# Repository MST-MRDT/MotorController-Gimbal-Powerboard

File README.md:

# MotorController-Gimbal-Powerboard

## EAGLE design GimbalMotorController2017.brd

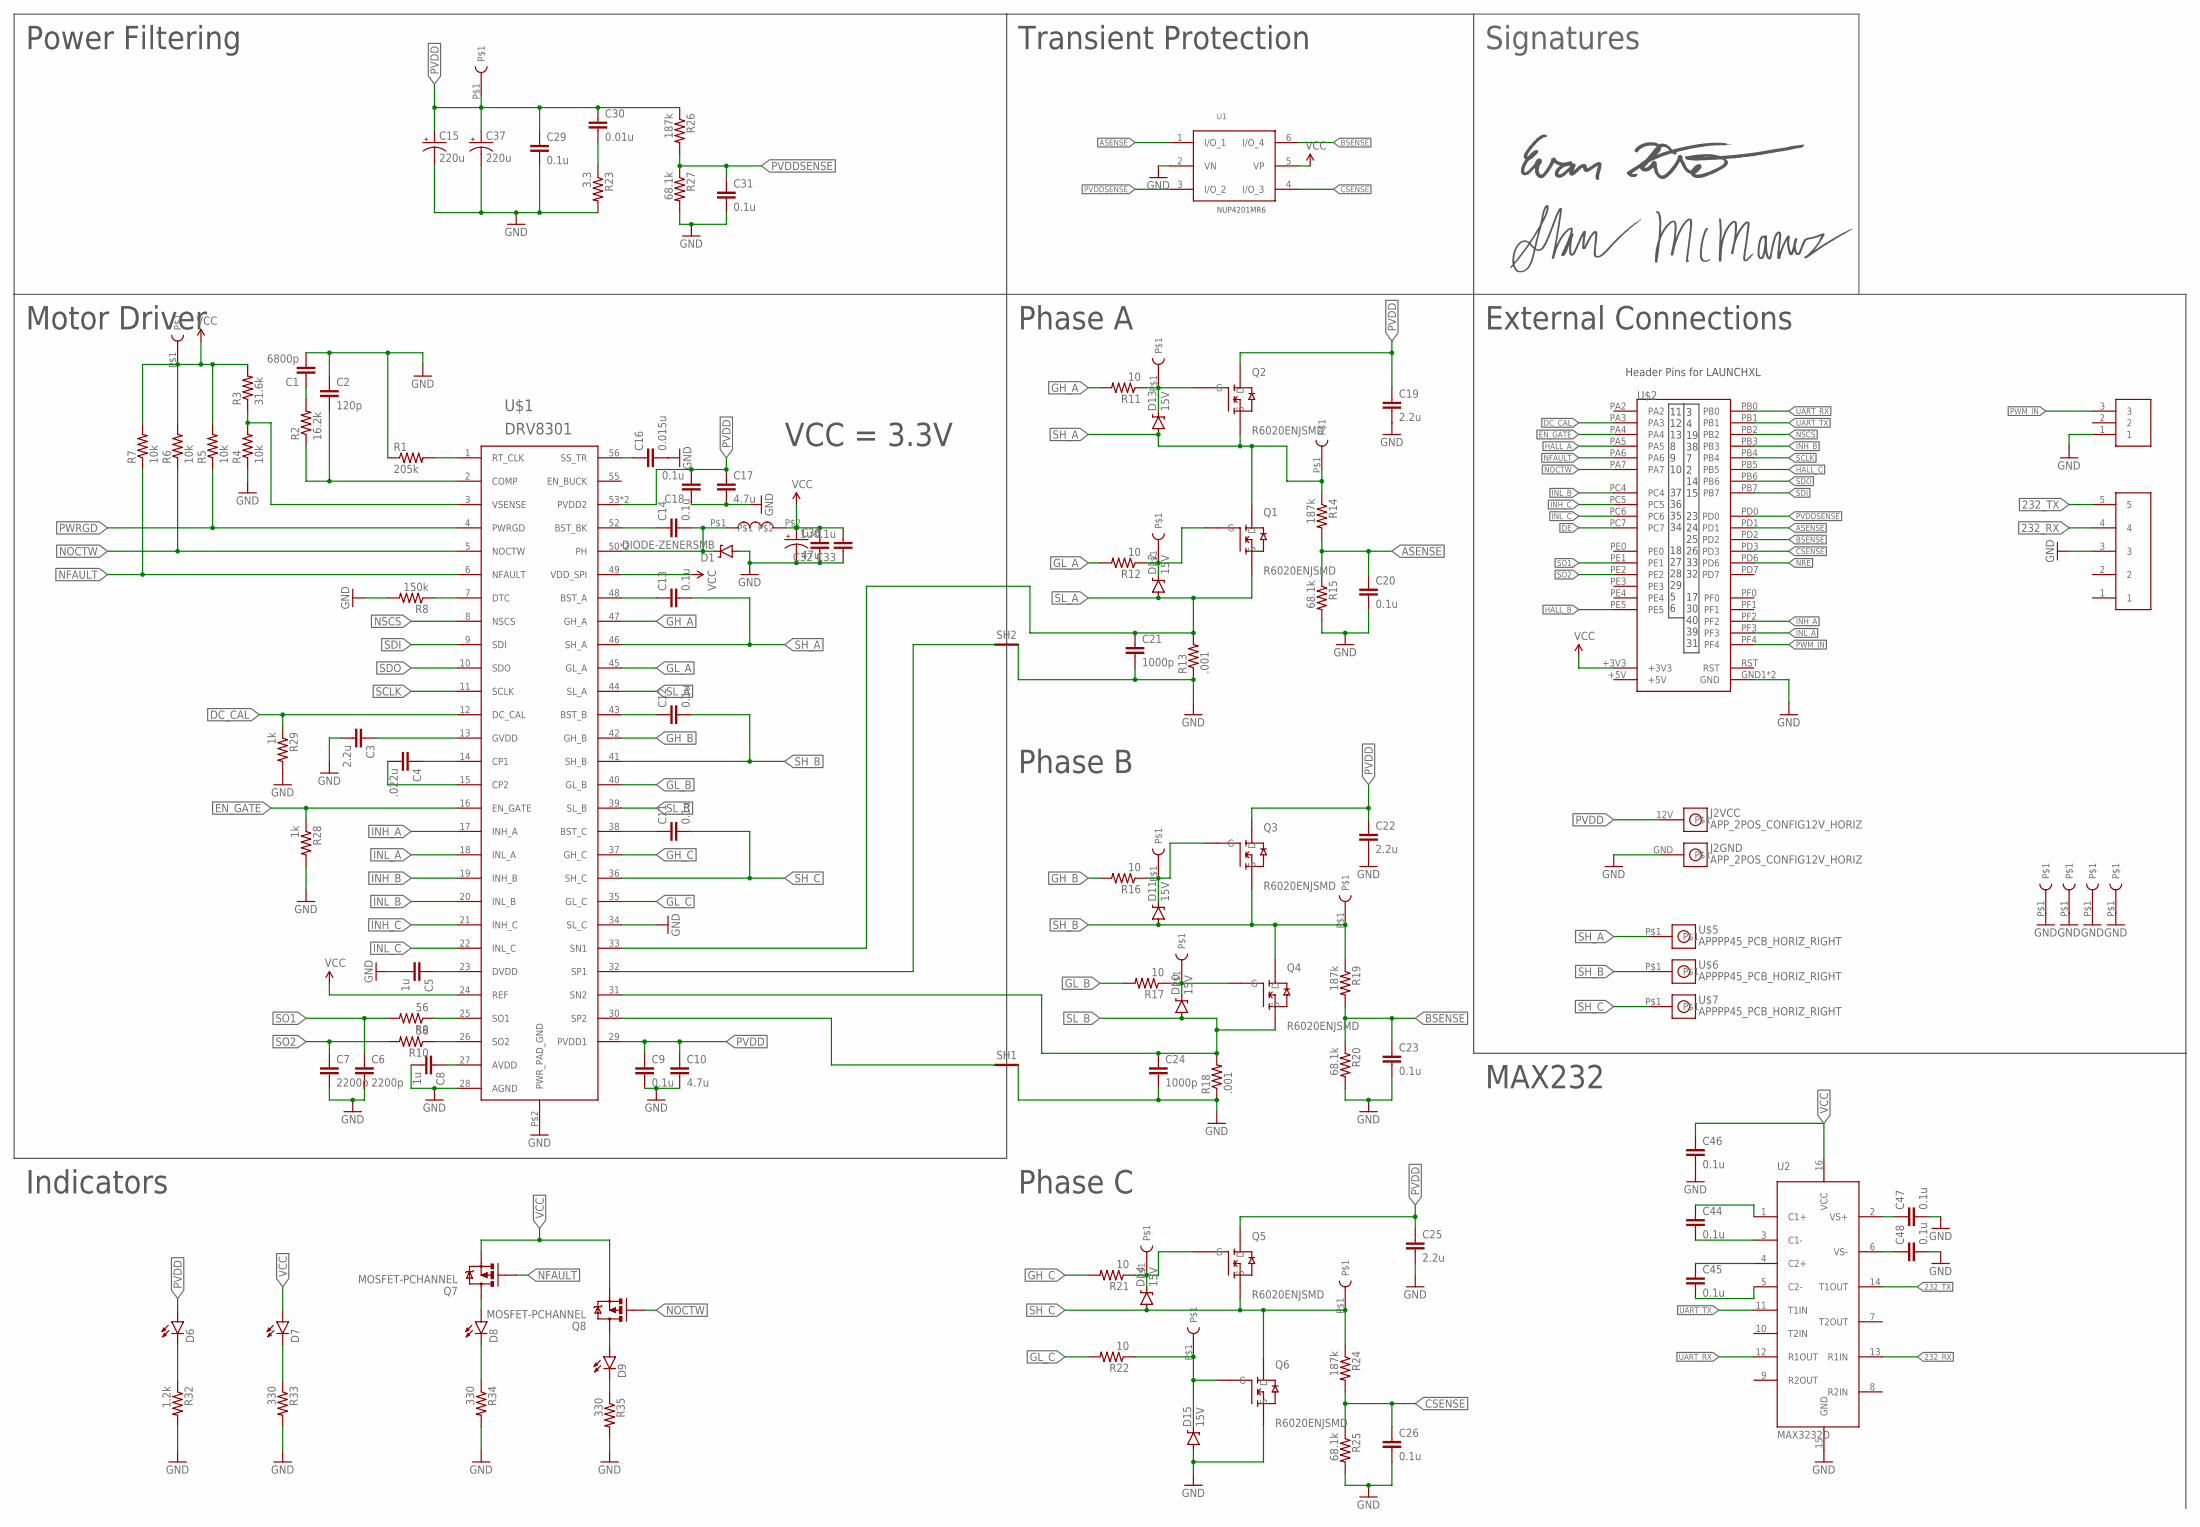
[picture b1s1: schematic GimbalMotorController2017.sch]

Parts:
C1: 6800p; 0805
C2: 120p; 0805
C3, C19, C22, C25: 2.2u; 1206
C4: .022u; 0805
C5, C8, C32: 1u; 0805
C6, C7: 2200p; 0805
C9, C11, C12, C13, C14, C18, C20, C23, C26, C29, C31, C33, C44, C45, C46, C47, C48: 0.1u; 0805
C10, C17: 4.7u; 1206
C15, C37: 220u; CPOL-RADIAL-1000UF-25V
C16: 0.015u; 0805
C21, C24: 1000p; 0805
C30: 0.01u; 0805
C36: 47u; CPOL-RADIAL-100UF-25V
D1: DIODE-ZENERSMB; SMB-DIODE
D6, D7, D8, D9: LED1206; LED-1206
D10, D11, D12, D13, D14, D15: 15V; SOD-323
J1: SL03THROUGH_HOLE; MOLEX_SL_03_TH
J2: APP_2POS_CONFIG12V_HORIZ; APP45_12V_HORIZ_CONFIG
Q1, Q2, Q3, Q4, Q5, Q6: R6020ENJSMD; D2PACK
Q7, Q8: MOSFET-PCHANNEL; SOT23-3
R1: 205k; 0805
R2: 16.2k; 0805
R3: 31.6k; 0805
R4, R5, R6, R7: 10k; 0805
R8: 150k; 0805
R9, R10: 56; 0805
R11, R12, R16, R17, R21, R22: 10; 0805
R13, R18: .001; 1206
R14, R19, R24, R26: 187k; 0805
R15, R20, R25, R27: 68.1k; 0805
R23: 3.3; 0805
R28, R29: 1k; 0805
R32: 1.2k; 0805
R33, R34, R35: 330; 0805
SH1, SH2: SHORT-HT5; SHORT_TOP-50
U1: NUP4201MR6; TSOP-6
U2: MAX3232D; SOIC16
U$1: DRV8301; TFSOP-56
U$2: TIVA-C
U$3, U$10, U$12, U$15, U$16, U$17, U$18, U$19, U$20, U$24, U$25, U$26, U$27, U$28, U$29: TEST_POINT_0.1INDIAM
U$4: 5PIN
U$5, U$6, U$7: APPPP45_PCB_HORIZ_RIGHT; APP45_PCB_HORIZ_RIGHT
U$8: SHAUN_MCMANUS_SIGNATURE
U$11: EVAN_HITE_SIGNATURE
U$14: 33u; INDUCTOR_DR74

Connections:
232_RX: U2.13 (R1IN), U$4.4
232_TX: U2.14 (T1OUT), U$4.5
+5V: U$2.+5V
ASENSE: C20.1, R14.2, R15.1, U1.1 (I/O_1), U$2.PD1
BSENSE: C23.1, R19.2, R20.1, U1.6 (I/O_4), U$2.PD2
CSENSE: C26.1, R24.2, R25.1, U1.4 (I/O_3), U$2.PD3
DC_CAL: R29.1, U$1.12 (DC_CAL), U$2.PA3
DE: U$2.PC7
EN_GATE: R28.1, U$1.16 (EN_GATE), U$2.PA4
GH_A: R11.2, U$1.47 (GH_A)
GH_B: R16.2, U$1.42 (GH_B)
GH_C: R21.2, U$1.37 (GH_C)
GL_A: R12.2, U$1.45 (GL_A)
GL_B: R17.2, U$1.40 (GL_B)
GL_C: R22.2, U$1.35 (GL_C)
GND: C1.2, C2.1, C3.2, C5.2, C6.2, C7.2, C8.2, C9.2, C10.2, C15.2 (-), C16.2, C17.2, C18.1, C19.2, C20.2, C21.2, C22.2, C23.2, C24.2, C25.2, C26.2, C29.2, C31.2, C32.1, C33.1, C36.2 (-), C37.2 (-), C46.2, C47.2, C48.2, D1.A, D15.A, J1.1, J2.GND, Q6.2 (S), R1.1, R4.1, R8.2, R13.1, R15.2, R18.1, R20.2, R23.2, R25.2, R27.2, R28.2, R29.2, R32.2, R33.2, R34.2, R35.2, SH1.2, SH2.2, U1.2 (VN), U2.15 (GND), U$1.28 (AGND), U$1.34 (SL_C), U$1.P$2 (PWR_PAD_GND), U$2.GND1 (GND), U$2.GND2 (GND), U$4.3, U$26.P$1, U$27.P$1, U$28.P$1, U$29.P$1
HALL_A: U$2.PA5
HALL_B: U$2.PE5
HALL_C: U$2.PB5
INH_A: U$1.17 (INH_A), U$2.PF2
INH_B: U$1.19 (INH_B), U$2.PB3
INH_C: U$1.21 (INH_C), U$2.PC5
INL_A: U$1.18 (INL_A), U$2.PF3
INL_B: U$1.20 (INL_B), U$2.PC4
INL_C: U$1.22 (INL_C), U$2.PC6
unnamed: C2.2, R2.1, U$1.2 (COMP)
unnamed: C1.1, R2.2
unnamed: R3.1, R4.2, U$1.3 (VSENSE)
unnamed: R1.2, U$1.1 (RT_CLK)
unnamed: R8.1, U$1.7 (DTC)
unnamed: C4.1, U$1.14 (CP1)
unnamed: C4.2, U$1.15 (CP2)
unnamed: C3.1, U$1.13 (GVDD)
unnamed: C5.1, U$1.23 (DVDD)
unnamed: R9.1, U$1.25 (SO1)
unnamed: R10.1, U$1.26 (SO2)
unnamed: C8.1, U$1.27 (AVDD)
unnamed: D13.C, Q2.1 (G), R11.1, U$12.P$1
unnamed: D11.C, Q3.1 (G), R16.1, U$16.P$1
unnamed: D10.C, Q4.1 (G), R17.1, U$17.P$1
unnamed: D12.C, Q1.1 (G), R12.1, U$15.P$1
unnamed: D14.C, Q5.1 (G), R21.1, U$18.P$1
unnamed: D15.C, Q6.1 (G), R22.1, U$19.P$1
unnamed: C11.1, U$1.38 (BST_C)
unnamed: C30.2, R23.1
unnamed: D6.C, R32.1
unnamed: D7.C, R33.1
unnamed: C12.1, U$1.43 (BST_B)
unnamed: D8.C, R34.1
unnamed: D9.C, R35.1
unnamed: D9.A, Q8.3 (D)
unnamed: C13.1, U$1.48 (BST_A)
unnamed: C14.1, U$1.52 (BST_BK)
unnamed: C14.2, D1.C, U$1.50 (PH), U$1.51 (PH), U$14.P$1
unnamed: D8.A, Q7.3 (D)
unnamed: C16.1, U$1.56 (SS_TR)
unnamed: C44.1, U2.1 (C1+)
unnamed: C44.2, U2.3 (C1-)
unnamed: C45.1, U2.4 (C2+)
unnamed: C45.2, U2.5 (C2-)
unnamed: C48.1, U2.6 (VS-)
unnamed: C47.1, U2.2 (VS+)
NFAULT: Q7.1 (G), R7.1, U$1.6 (NFAULT), U$2.PA6
NOCTW: Q8.1 (G), R6.1, U$1.5 (NOCTW), U$2.PA7
NRE: U$2.PD6
NSCS: U$1.8 (NSCS), U$2.PB2
PVDD: C9.1, C10.1, C15.1 (+), C17.1, C18.2, C19.1, C22.1, C25.1, C29.1, C30.1, C37.1 (+), D6.A, J2.12V, Q2.TAB (D), Q3.TAB (D), Q5.TAB (D), R26.1, U$1.29 (PVDD1), U$1.53 (PVDD2), U$1.54 (PVDD2), U$3.P$1
PVDDSENSE: C31.1, R26.2, R27.1, U1.3 (I/O_2), U$2.PD0
PWM_IN: J1.3, U$2.PF4
PWRGD: R5.1, U$1.4 (PWRGD)
RST: U$2.RST
SCLK: U$1.11 (SCLK), U$2.PB4
SDI: U$1.9 (SDI), U$2.PB7
SDO: U$1.10 (SDO), U$2.PB6
SH_A: C13.2, D13.A, Q1.TAB (D), Q2.2 (S), R14.1, U$1.46 (SH_A), U$5.P$1, U$25.P$1
SH_B: C12.2, D11.A, Q3.2 (S), Q4.TAB (D), R19.1, U$1.41 (SH_B), U$6.P$1, U$24.P$1
SH_C: C11.2, D14.A, Q5.2 (S), Q6.TAB (D), R24.1, U$1.36 (SH_C), U$7.P$1, U$20.P$1
SL_A: C21.1, D12.A, Q1.2 (S), R13.2, U$1.33 (SN1), U$1.44 (SL_A)
SL_B: C24.1, D10.A, Q4.2 (S), R18.2, U$1.31 (SN2), U$1.39 (SL_B)
SO1: C6.1, R9.2, U$2.PE1
SO2: C7.1, R10.2, U$2.PE2
SP1: SH2.1, U$1.32 (SP1)
SP2: SH1.1, U$1.30 (SP2)
UART_RX: U2.12 (R1OUT), U$2.PB0
UART_TX: U2.11 (T1IN), U$2.PB1
VCC: C32.2, C33.2, C36.1 (+), C46.1, D7.A, Q7.2 (S), Q8.2 (S), R3.2, R5.2, R6.2, R7.2, U1.5 (VP), U2.16 (VCC), U$1.24 (REF), U$1.49 (VDD_SPI), U$2.+3V3, U$10.P$1, U$14.P$2

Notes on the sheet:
11 12 13 8 9 10 37 36 35 34 18 27 28 29 5 6
3 4 19 38 7 2 14 15 23 24 25 26 33 32 17 30 40 39 31
Header Pins for LAUNCHXL
Power Filtering
Motor Driver
Transient Protection
Phase A
Phase B
Phase C
External Connections
Indicators
VCC = 3.3V
MAX232
Signatures

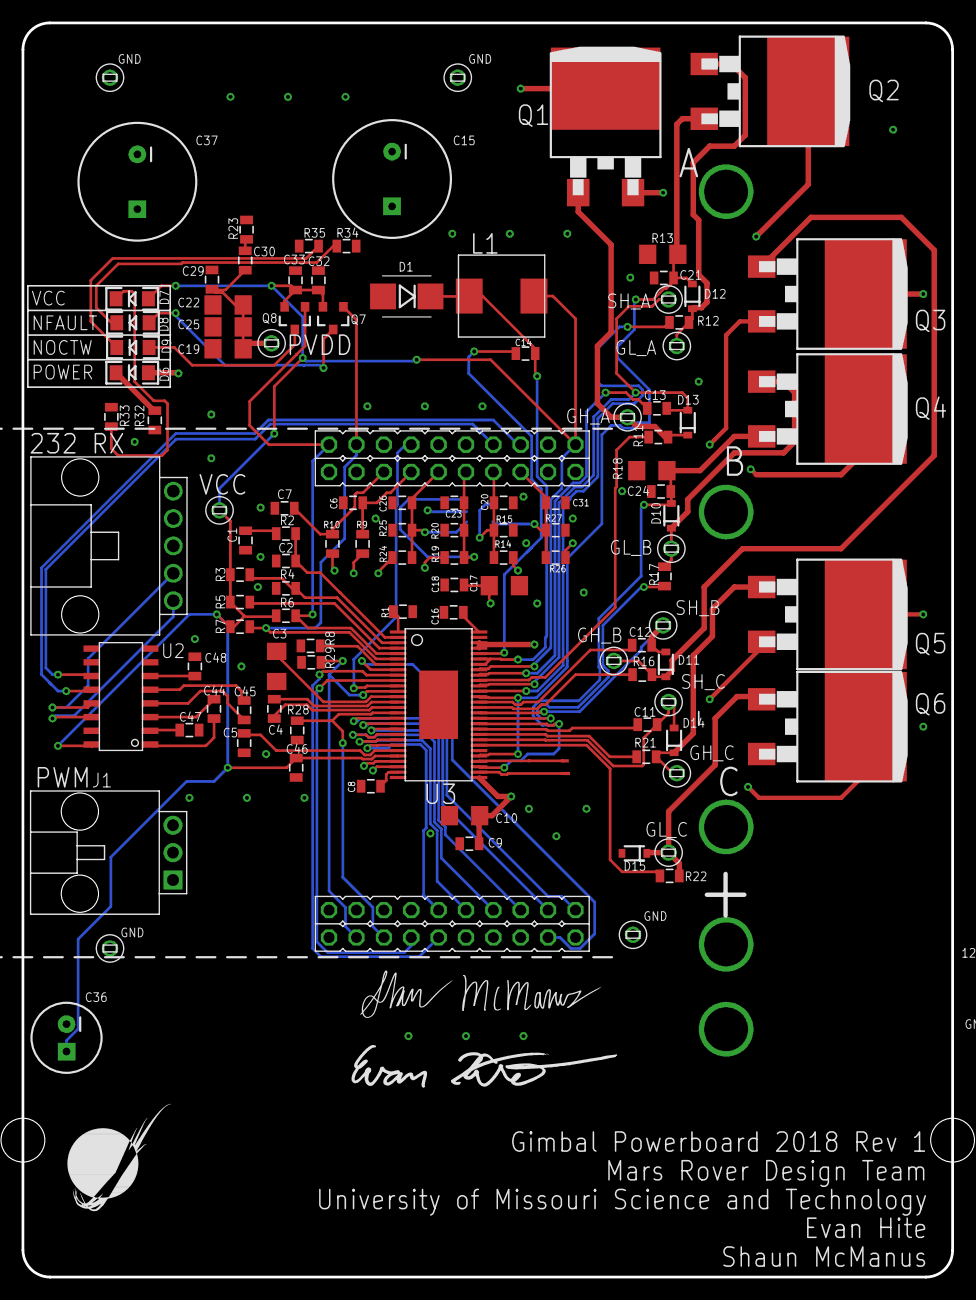
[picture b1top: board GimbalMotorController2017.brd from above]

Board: 4 copper layers, 86.2 x 116.3 mm, 121 parts (1 on the bottom side), 79 nets.

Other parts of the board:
U$9: MRDT_LOGO

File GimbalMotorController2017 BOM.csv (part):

Partlist exported from C:/Users/shotp/Documents/GitHub/MotorController-Gimbal-Powerboard/Gimbal Board/GimbalMotorController2017.sch at 1/24/2018 7:39 PM

Part Value                    Device                   Package                Description                                   BOM COLOR1 COLOR2 OPERATING_VOLTAGE ORIENT PARTNO     PROD_ID     VALUE
C1   6800p                    CAP0805                  0805                   Capacitor                                                                                                            
C2   120p                     CAP0805                  0805                   Capacitor                                                                                                            
C3   2.2u                     CAP1206                  1206                   Capacitor                                                                                                            
C4   .022u                    CAP0805                  0805                   Capacitor                                                                                                            
C5   1u                       CAP0805                  0805                   Capacitor                                                                                                            
C6   2200p                    CAP0805                  0805                   Capacitor                                                                                                            
C7   2200p                    CAP0805                  0805                   Capacitor                                                                                                            
C8   1u                       CAP0805                  0805                   Capacitor                                                                                                            
C9   0.1u                     CAP0805                  0805                   Capacitor                                                                                                            
C10  4.7u                     CAP1206                  1206                   Capacitor                                                                                                            
C11  0.1u                     CAP0805                  0805                   Capacitor                                                                                                            
C12  0.1u                     CAP0805                  0805                   Capacitor                                                                                                            
C13  0.1u                     CAP0805                  0805                   Capacitor                                                                                                            
C14  0.1u                     CAP0805                  0805                   Capacitor                                                                                                            
C15  220u                     CAP_POLPTH4              CPOL-RADIAL-1000UF-25V Capacitor Polarized                                                                                                  
C16  0.015u                   CAP0805                  0805                   Capacitor                                                                                                            
C17  4.7u                     CAP1206                  1206                   Capacitor                                                                                                            
C18  0.1u                     CAP0805                  0805                   Capacitor                                                                                                            
C19  2.2u                     CAP1206                  1206                   Capacitor                                                                                                            
C20  0.1u                     CAP0805                  0805                   Capacitor                                                                                                            
C21  1000p                    CAP0805                  0805                   Capacitor                                                                                                            
C22  2.2u                     CAP1206                  1206                   Capacitor                                                                                                            
C23  0.1u                     CAP0805                  0805                   Capacitor                                                                                                            
C24  1000p                    CAP0805                  0805                   Capacitor                                                                                                            
C25  2.2u                     CAP1206                  1206                   Capacitor                                                                                                            
C26  0.1u                     CAP0805                  0805                   Capacitor                                                                                                            
C29  0.1u                     CAP0805                  0805                   Capacitor                                                                                                            
C30  0.01u                    CAP0805                  0805                   Capacitor                                                                                                            
C31  0.1u                     CAP0805                  0805                   Capacitor                                                                                                            
C32  1u                       CAP0805                  0805                   Capacitor                                                                                                            
C33  0.1u                     CAP0805                  0805                   Capacitor                                                                                                            
C36  47u                      CAP_POLPTH1              CPOL-RADIAL-100UF-25V  Capacitor Polarized                                                                                                  
C37  220u                     CAP_POLPTH4              CPOL-RADIAL-1000UF-25V Capacitor Polarized                                                                                                  
C44  0.1u                     CAP0805                  0805                   Capacitor                                                                                                            
C45  0.1u                     CAP0805                  0805                   Capacitor                                                                                                            
C46  0.1u                     CAP0805                  0805                   Capacitor                                                                                                            
C47  0.1u                     CAP0805                  0805                   Capacitor                                                                                                            
C48  0.1u                     CAP0805                  0805                   Capacitor                                                                                                            
D1   DIODE-ZENERSMB           DIODE-ZENERSMB           SMB-DIODE              Zener Diode                                                                                                          
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
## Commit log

2017-11-05 initial commit with Cameron's reference
2017-11-08 changed power filtering cap count and R26 value for 12v to 3.3v conversion
2017-11-10 added CSD18533Q5A fets to Phase C in place of previously used fets
2017-11-10 added CSD18533Q5A fets to Phase B in place of the previously used fets
2017-11-10 added CSD18533Q5A fets to Phase A in place of previously used fets. Cleaned up schematic.
2017-11-10 adjusted phase resistor values for 12v to 3.3v voltage divider
2017-11-10 removed hall effect sensor connector
2017-11-10 Shrank size to roughly 11 square inches, moved lots of components and ripped up wires
2017-11-10 Add pwm connector to external connections
2017-11-10 Started routing traces on board
2017-11-12 Updated silkscreen by removing hall effect sensor indicator and Cameron's signature, mounting holes were squared and board was straightened
2017-11-16 Testing a new board layout by moving the fets and andersons to the right of the board. MAX3232 has also been moved to the left closer to its connector
2017-11-16 Finished arranging test points, beginning traces
2017-11-16 Started Routing
    Connected a lot of components and have started the routing process
2017-11-26 Routed traces for external connections, caps, and a few diodes. Most traces completed except for fet traces.
2017-11-26 Finished Tracing
    All clearance issues have been fixed. The board's tracing issues have been fixed. All overlap issues have been fixed. It is now ready for Board Review.
2017-11-26 Shrank Board
    Board is now smaller
2017-11-30 Smashed and Via Patched the Board
    Almost every surface mount now has a via connecting it to the other three ground plains. Silkscreen is a WIP.
2017-11-30 Silk Screen Improvement
2017-12-01 Updated silkscreen and moved a cap
    Made some slight clarity changes for better readability
2017-12-04 Updated Board
    Now board is updated
2017-12-04 Board Updated for Board Review
2017-12-18 Fixed certain silkscreen issues and routing
    LED's are now fully labelled and in easy to see places
2017-12-18 Forgot to include the schematic for the board
2017-12-22 Changed Resistor values for 15v to 3.3v conversion.
    Changed resistor values for 15v to 3.3v conversion. Bumped up the magnitude by 10x per board review #1 suggestions.
2017-12-23 Changed Fets Around and redid routing
    Fets are now ABC, instead of CBA. This made for easier routing. Silkscreen is updated and the LED's are properly labelled. FET models are still unchanged. Routing has been cleaned up to the best of m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
2017-12-23 Reorganized schematic sections
    Added new section for MAX232 and reorganized External connections for clarity
2017-12-23 Edited label size for neatness and consistency
2017-12-29 Moved Max232 to avoid bridging with SL connectors
2018-01-14 Added new FET package, reorganized schematic to further clean up the labeling
2018-01-15 Updated resistor values to give 3.2v/15v ratio with resistors known to be available on digikey with the 0805 package
2018-01-15 Added Vertical Mounting Wing. Integrated New Fets adjusted andersons for Control Card
    0.5 Inches of the Board has been added for a vertical mounting wing. Routing for new fets has been made. Board has been increased in size significantly. Basic Silkscreen adjustments have been made. B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
2018-01-21 Added Vertical mounting wing
2018-01-21 Fixed ERC issue
2018-01-22 Updated resistor values for new divider, updated indicators section, changed PWM_IN_NO_FILTER to PWM_IN and removed previous PWM_IN label
    Resistor values updated for 12v to 3.2v ratio. Simplified D6 indicator schematic to be just an LED, resistor, power, and ground. Changed old PWM_IN_NO_FILTER label to PWM_IN in external connections, 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
2018-01-22 Board routing was cleaned up. Silkscreen was cleaned up. Correct Package for Power Anderson Connectors is now being used.
    Mounting holes were removed. SL connectors were labelled. All test points are correctly named. More vias have been added to stitch the planes together. Traces were redrawn in many places for cleaner 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
2018-01-22 Silscreen Update
    Added arrows to aid in putting cards together.
2018-01-23 Silkscreen Update and Dimension update
    Silkscreen was added for the inductor as well as all the Fets. Dimension of the board was alterred to accomodate a vertical mount with extra headroom to prevent any mechanical complications.
2018-01-24 Another Silkscreen update
    LED's silkscreen was added for better visibility.
2018-01-25 Added a bill of materials
2018-01-25 Fixed LED positions
2018-01-28 Vertical Mounting drill hole size increased
2018-01-29 Added Signatures and BOM file is now text file
2018-03-11 Initial upload of KiCAD Gimbal Powerboard
2018-03-11 Replaced legacy LaunchXL headers with new LaunchXL header device in schematic
2018-03-11 Github Fix Commit
2018-03-11 Removed outdated BOM
2018-03-11 Removed gitignore and properly added .pro file
2018-03-14 Started device/package pairing
2018-03-14 Paired devices and packages for all components of schematic except MAX3232
2018-03-14 Finished pairing devices with packages and generated netlist
2018-03-14 Added preliminary adjustments for current sensor implementation
2018-03-18 Added current sensor
2018-04-01 Added netlist, updated drv8301 implementation
2018-04-01 Adjusted circuit implementation of DRV8301, adjusted FETs for LED indicators to have correct orientation for pads
2018-04-01 Finished troubleshooting all netlist read errors, final push before board construction
2018-04-01 Final netlist
2018-04-08 Changed MAX3232 device, updated GND and VCC flags, added 100k pull down resistor in parallel with zener diode, added diode across 10 ohm resistor for all phases, added flags for motor terminal A,B,C
2018-04-09 Initial PCB layout with 2P2T switch for PWM, INL_C
2018-04-12 Sorted PCB components, preliminary layout
2018-04-13 Created traces for MAX3232, part of DRV8301
2018-04-13 Finished component placement for DRV8301, phase C
2018-04-14 Added components for phase B circuitry
2018-04-14 Finished component placement, beginning the last of traces and silkscreen work
2018-04-14 Finished routing for DRV8301
2018-04-14 More routing progress, most of the top third of the board is completed
2018-04-15 Finished all routing
2018-04-15 Added silkscreen for indicator LEDs and 2P2T switch
2018-04-15 Added ground copper layer, silkscreen for serial, pwm, phase connections, removed test point for MTC. Finished round 1 board review with Judah, Andrew, Jacob
2018-04-15 Updated footprint for Tiva SMD J1 header shield
2018-04-16 Updated flags to be directional
2018-04-16 Generated gerbs
2018-04-16 Final gerb generation
2018-04-16 Updated tiva shield with fixed version, generated fresh gerbs
2018-04-18 Added Atlas Logo!
2018-04-18 Made some quick fixes to the silkscreen after quintuple checking the gerbs
2018-04-18 Fixed an issue with drill holes not rendering properly in gerb viewers. Generated fixed gerbs and updated the zip file
2018-04-18 Made some last minute adjustments to the silkscreen for clarity

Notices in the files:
parts and their libraries:
SparkFun-Passives: Licensing: Creative Commons ShareAlike 4.0 International - https://creativecommons.org/licenses/by-sa/4.0
